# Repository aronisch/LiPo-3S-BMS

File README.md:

# LiPo-3S-BMS
Battery Management System based on bq78350R1 and bq79620 - Designed for 3S LiPo batteries

- Originally created for the [INSA Rennes robot club](https://github.com/clubrobot)
- Schematics and PCB made with Autodesk Eagle
- FETs controlled on the low-side (communication based on ground connection not possible outside the BMS)
- Allow the atmega on the pcb to get the SoC, the voltage, current, remaining time and all the information available from the bq78350R1 (small C++ class using Arduino Wire provided)
- Version 1.1 removes the temperature sensor connector, has a smaller footprint and add a SMB connector for the EV2400 which is the development module necessary to interface the BMS with bqStudio on PC.

## TODO
- Reduce footprint even further
- Change FET control to high-side
- Look for alternatives to the atmega to get battery status (maybe remove it or put the 5V regulator after the protection)
- Use right-angle connectors instead of straight ones
- Better protect SMB port
- Use XT90 Connectors instead of Dean ?

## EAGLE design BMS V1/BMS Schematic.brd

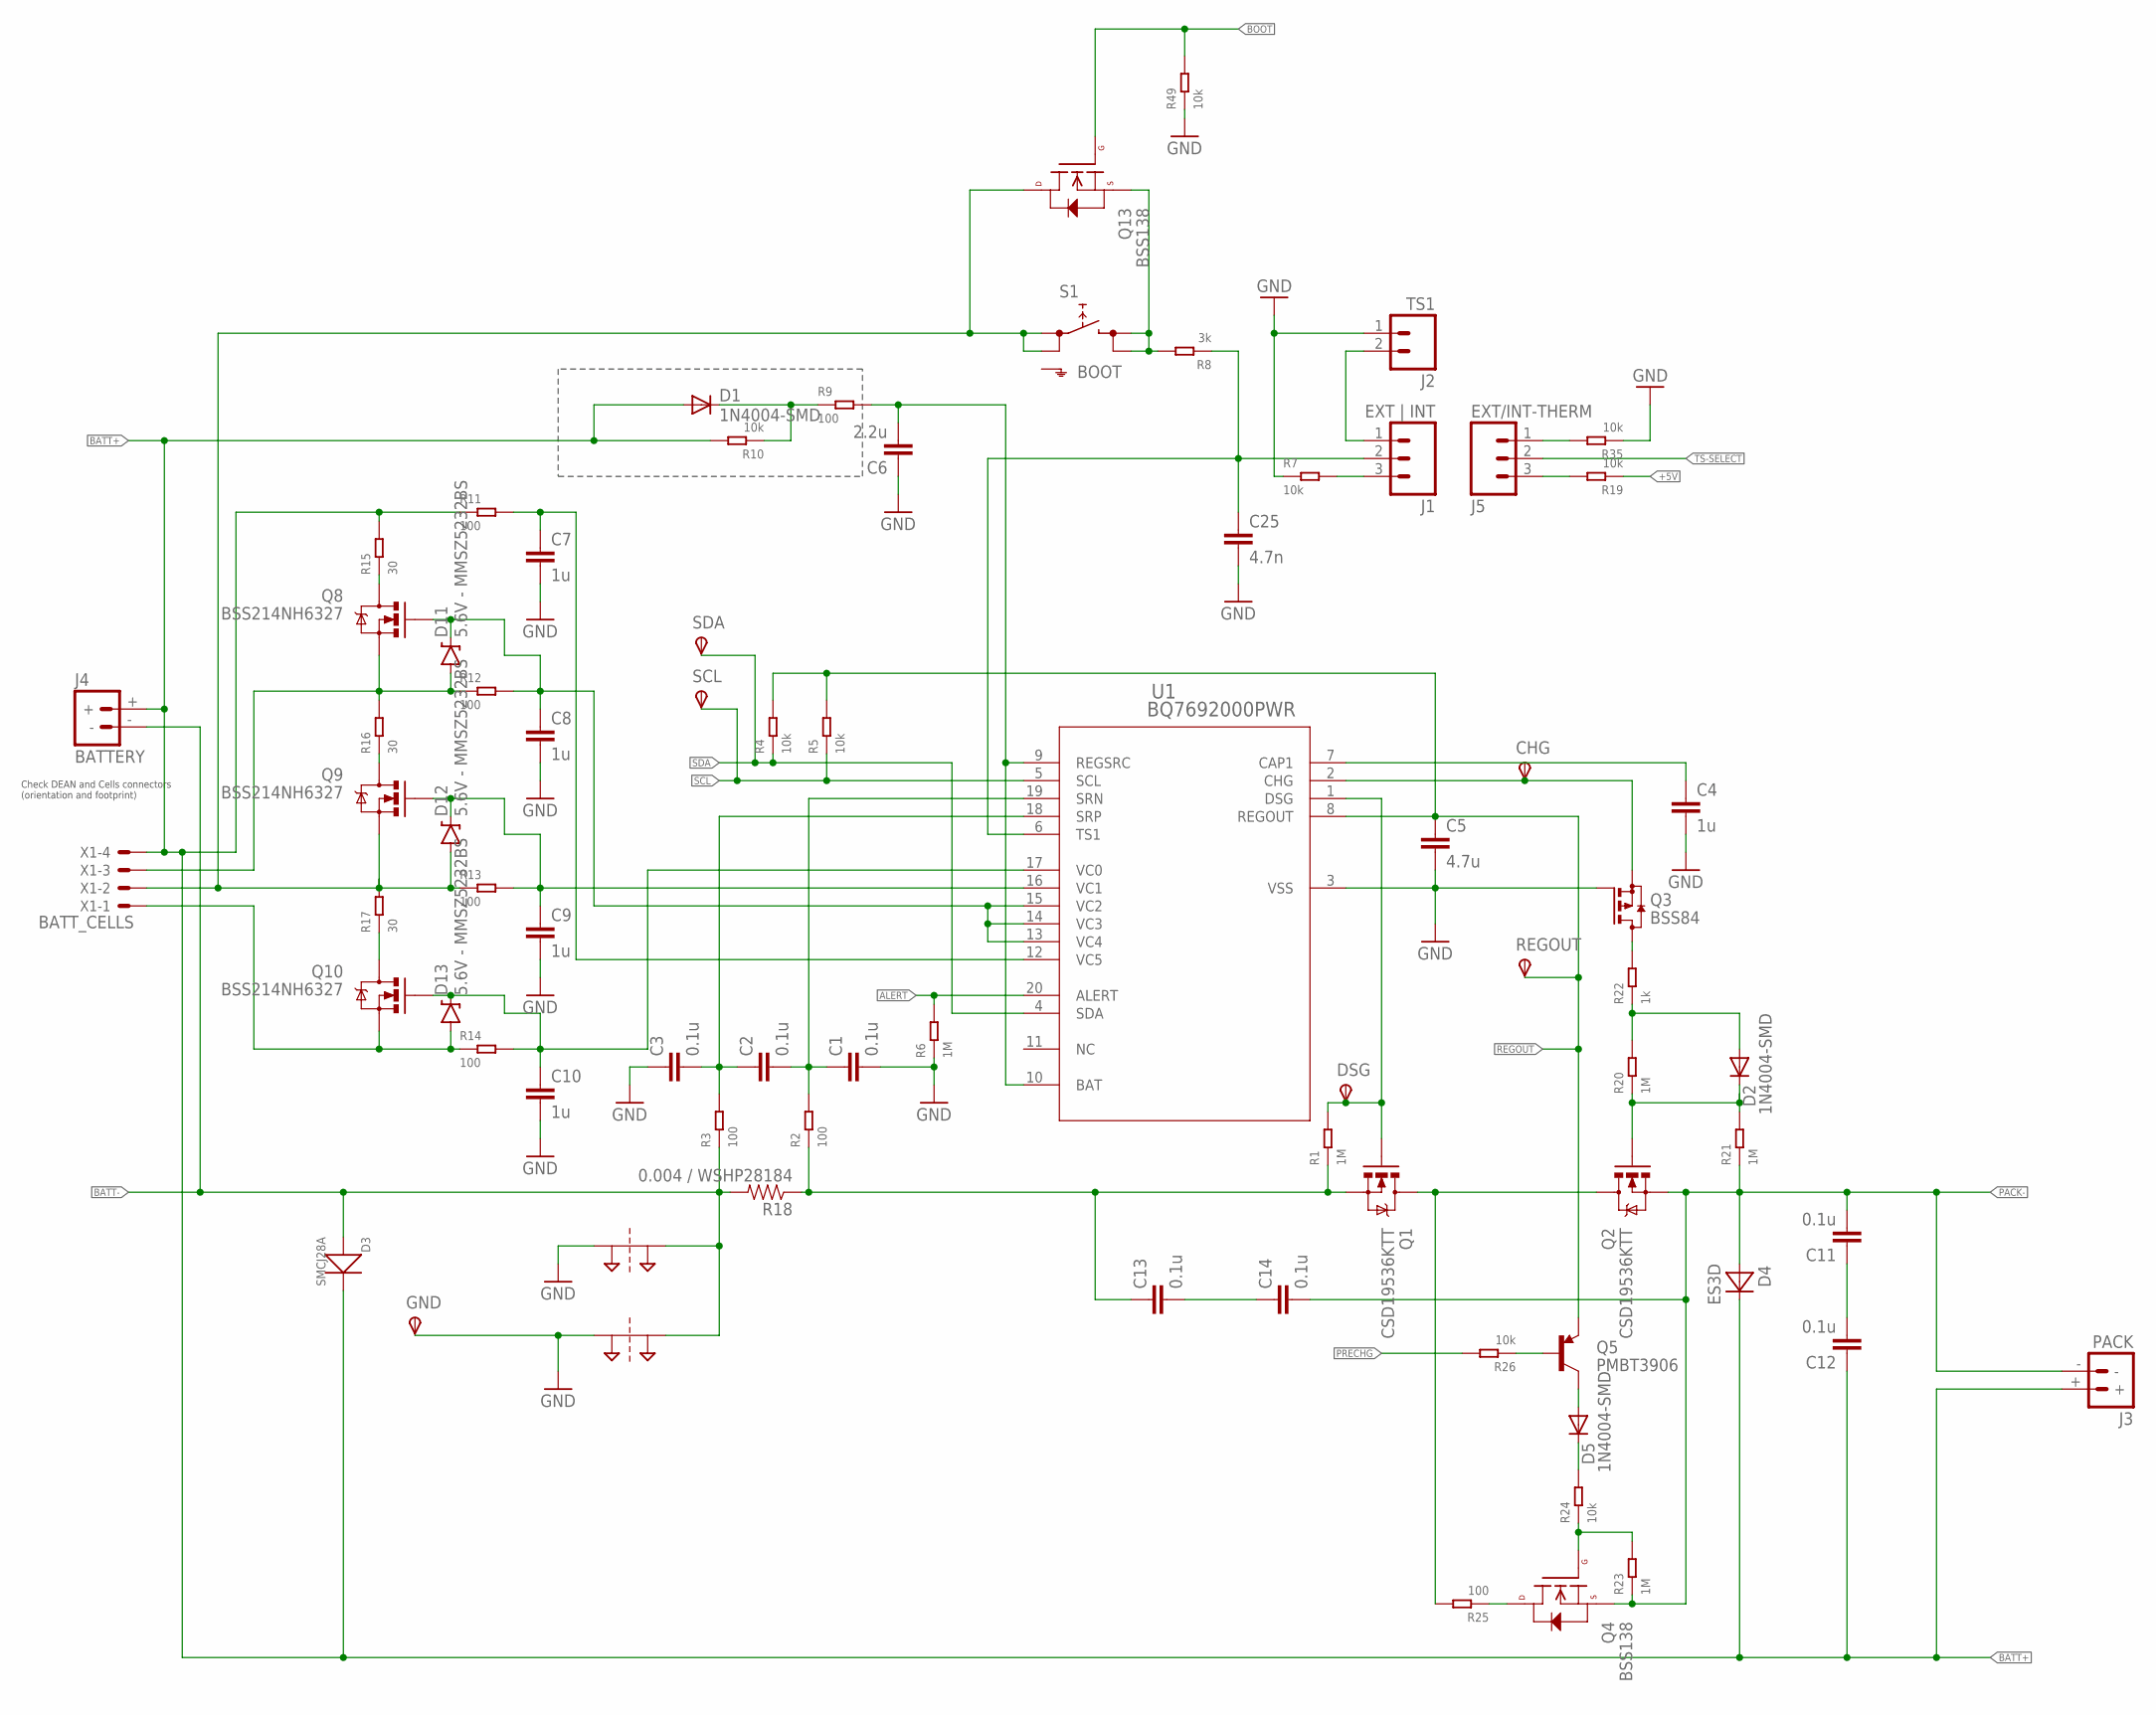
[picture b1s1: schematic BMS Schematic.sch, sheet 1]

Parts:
C1, C2, C3, C11, C12, C13, C14: 0.1u; 0805
C4, C7, C8, C9, C10: 1u; 0805
C5: 4.7u; 0805
C6: 2.2u; C1206
C25: 4.7n; 0805
CHG: TPSB2,54; B2,54
D1, D2, D5: 1N4004-SMD; DO-214
D3: SMCJ28A; DO-214AB
D4: ES3D; SMC
D11, D12, D13: 5.6V - MMSZ5232BS; SOD-323
DSG: TPSB2,54; B2,54
GND: GND; P1-17
J1: EXT | INT; 1X03
J2: TS1; 1X02
J3: PACK; DEANS
J4: BATTERY; DEANS
J5: EXT/INT-THERM; 1X03
PT1, PT2: 2PT_GND_TIE
Q1, Q2: CSD19536KTT; TO-263/D2PAK
Q3: BSS84; SOT23
Q4, Q13: BSS138; SOT23-3
Q5: PMBT3906; SOT23-3
Q8, Q9, Q10: BSS214NH6327; SOT23-3
R1, R6, R20, R21, R23: 1M; R0805
R2, R3, R9, R11, R12, R13, R14: 100; R0805
R4, R5, R7, R10, R19, R24, R26, R35, R49: 10k; R0805
R8: 3k; R0805
R15, R16, R17: 30; R2512
R18: 0.004 / WSHP28184; 2512
R22: 1k; R0805
R25: 100; R2512
REGOUT: TPSB2,54; B2,54
S1: BOOT; SKHMPXE010
SCL: TPSB2,54; B2,54
SDA: TPSB2,54; B2,54
U1: BQ7692000PWR; PW20
X1: BATT_CELLS; 70543-04

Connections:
+5V: R19.1; also elsewhere on the board
ALERT: R6.2, U1.20 (ALERT); also elsewhere on the board
BATT+: C12.1, D1.A, D3.2 (-), D4.C, J3.+, J4.+, R10.2, R11.1, R15.2, X1.4; also elsewhere on the board
BATT-: D3.1 (+), J4.-, PT1.P$2, PT2.P$2, R3.1, R18.2
BOOT: Q13.1 (G), R49.2; also elsewhere on the board
CHG: CHG.TP, Q3.2 (S), U1.2 (CHG)
DSG: DSG.TP, Q1.1 (G), R1.2, U1.1 (DSG)
DSG-CHG: Q1.2 (D), Q2.2 (D), R25.2
GND: C1.2, C3.1, C4.2, C5.2, C6.1, C7.2, C8.2, C9.2, C10.2, C25.2, GND.TP, J2.1, PT1.P$1, PT2.P$1, Q3.1 (G), R6.1, R7.1, R35.1, R49.1, U1.3 (VSS); also elsewhere on the board
unnamed: C2.1, C3.2, R3.2, U1.18 (SRP)
unnamed: C1.1, C2.2, R2.2, U1.19 (SRN)
unnamed: C25.1, J1.2, R8.1, U1.6 (TS1)
unnamed: C6.2, R9.2, U1.9 (REGSRC), U1.10 (BAT)
unnamed: C4.1, U1.7 (CAP1)
unnamed: J1.1, J2.2
unnamed: J1.3, R7.2
unnamed: D1.C, R9.1, R10.1
unnamed: Q13.2 (S), R8.2, S1.3 (2.1), S1.4 (2.2)
unnamed: D13.A, Q10.2 (S), R14.1, X1.1
unnamed: C7.1, R11.2, U1.12 (VC5)
unnamed: Q8.3 (D), R15.1
unnamed: C10.1, D13.C, Q10.1 (G), R14.2, U1.17 (VC0)
unnamed: J5.3, R19.2
unnamed: D11.A, Q8.2 (S), R12.1, R16.2, X1.3
unnamed: Q9.3 (D), R16.1
unnamed: D2.C, Q2.1 (G), R20.1, R21.2
unnamed: C8.1, D11.C, Q8.1 (G), R12.2, U1.13 (VC4), U1.14 (VC3), U1.15 (VC2)
unnamed: Q10.3 (D), R17.1
unnamed: C11.1, C12.2
unnamed: D2.A, R20.2, R22.1
unnamed: D12.A, Q9.2 (S), Q13.3 (D), R13.1, R17.2, S1.1 (1.1), S1.2 (1.2), X1.2
unnamed: Q3.3 (D), R22.2
unnamed: C13.2, C14.1
unnamed: Q4.1 (G), R23.2, R24.1
unnamed: D5.C, R24.2
unnamed: D5.A, Q5.3 (C)
unnamed: Q5.1 (B), R26.1
unnamed: Q4.3 (D), R25.1
unnamed: J5.1, R35.2
unnamed: C9.1, D12.C, Q9.1 (G), R13.2, U1.16 (VC1)
PACK-: C11.2, C14.2, D4.A, J3.-, Q2.3 (S), Q4.2 (S), R21.1, R23.1
PRECHG: R26.2; also elsewhere on the board
REGOUT: C5.1, Q5.2 (E), R4.2, R5.2, REGOUT.TP, U1.8 (REGOUT); also elsewhere on the board
RSNS-DSG: C13.1, Q1.3 (S), R1.1, R2.1, R18.1
SCL: R5.1, SCL.TP, U1.5 (SCL); also elsewhere on the board
SDA: R4.1, SDA.TP, U1.4 (SDA); also elsewhere on the board
TS-SELECT: J5.2; also elsewhere on the board

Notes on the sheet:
Check DEAN and Cells connectors (orientation and footprint)

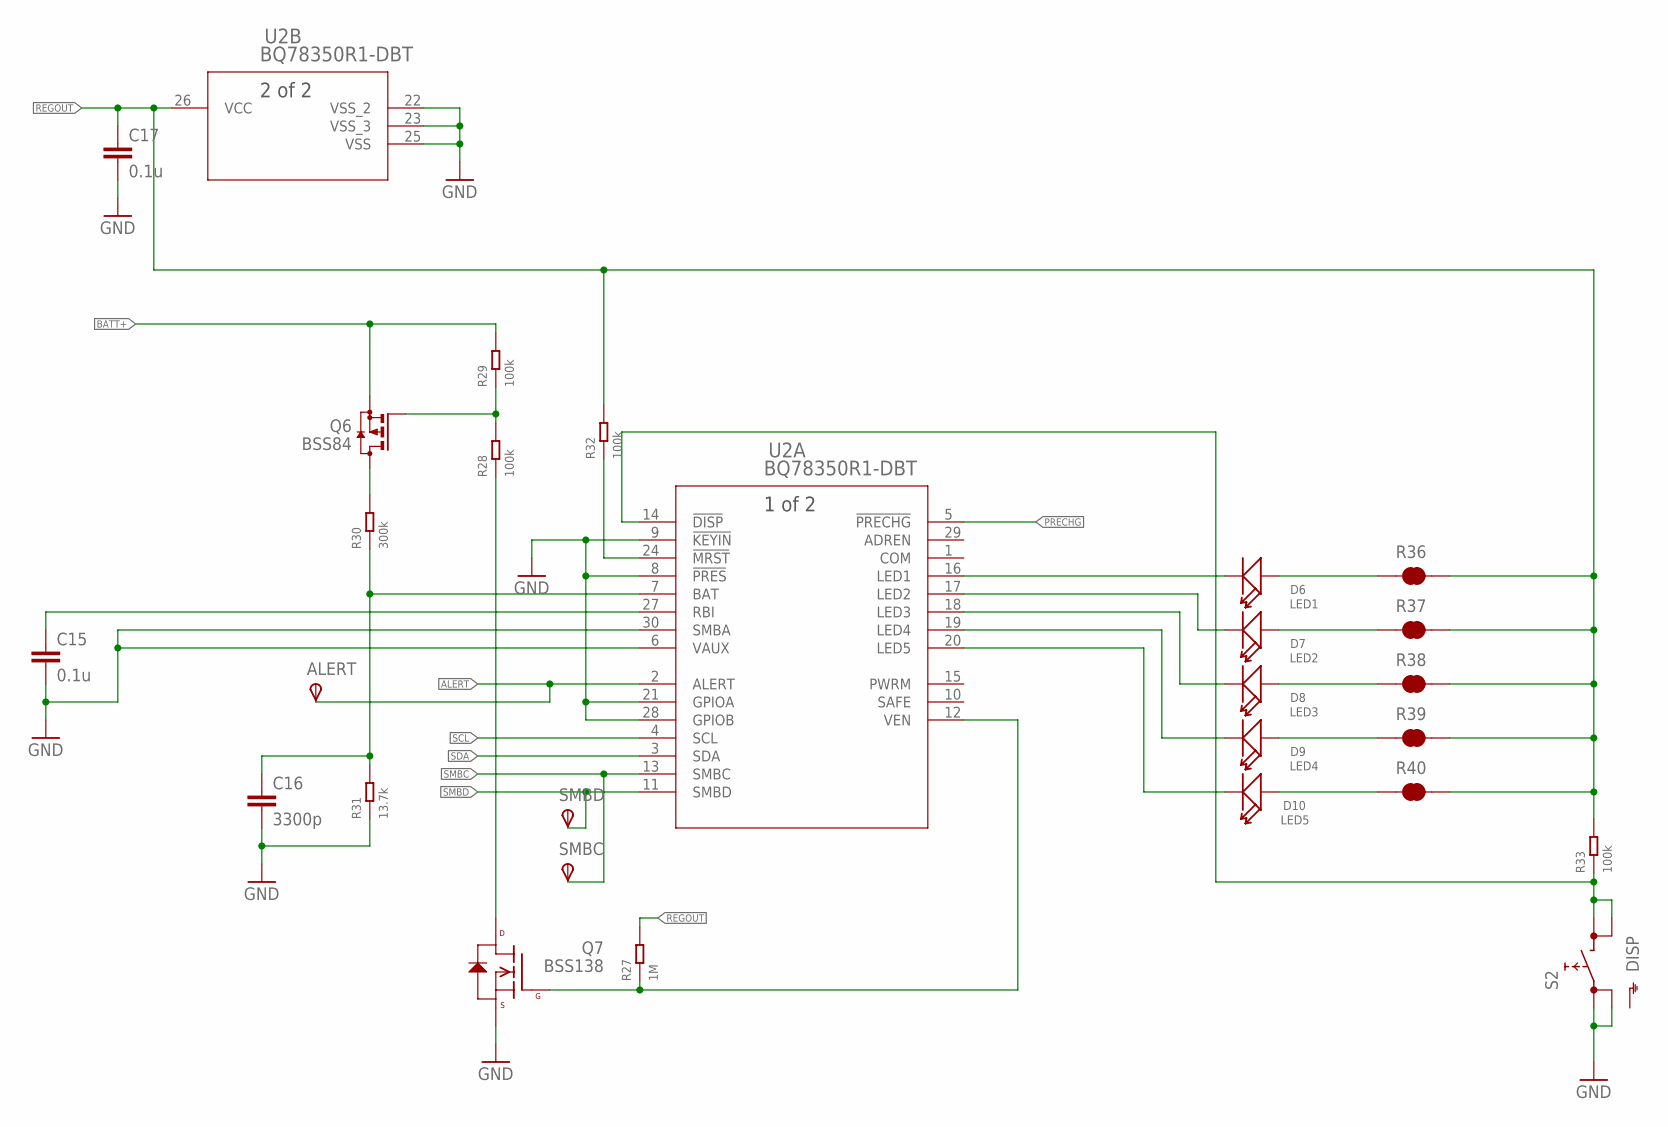
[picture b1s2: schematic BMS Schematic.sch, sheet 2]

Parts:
ALERT: TPSB2,54; B2,54
C15, C17: 0.1u; 0805
C16: 3300p; 0805
D6: LED1; LED-0805
D7: LED2; LED-0805
D8: LED3; LED-0805
D9: LED4; LED-0805
D10: LED5; LED-0805
Q6: BSS84; SOT23
Q7: BSS138; SOT23-3
R27: 1M; R0805
R28, R29, R32, R33: 100k; R0805
R30: 300k; R0805
R31: 13.7k; R0805
R36, R37, R38, R39, R40: JUMPER-NC-0805; R0805
S2: DISP; SKHMPXE010
SMBC: TPSB2,54; B2,54
SMBD: TPSB2,54; B2,54
U2: BQ78350R1-DBT; DBT30

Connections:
ALERT: ALERT.TP, U2.2 (ALERT); also elsewhere on the board
BATT+: Q6.2 (S), R29.2; also elsewhere on the board
GND: C15.2, C16.2, C17.2, Q7.2 (S), R31.1, S2.1 (1.1), S2.2 (1.2), U2.6 (VAUX), U2.8 (!PRES), U2.9 (!KEYIN), U2.21 (GPIOA), U2.22 (VSS_2), U2.23 (VSS_3), U2.25 (VSS), U2.28 (GPIOB), U2.30 (SMBA); also elsewhere on the board
unnamed: C15.1, U2.27 (RBI)
unnamed: Q7.1 (G), R27.1, U2.12 (VEN)
unnamed: Q7.3 (D), R28.1
unnamed: Q6.1 (G), R28.2, R29.1
unnamed: Q6.3 (D), R30.2
unnamed: C16.1, R30.1, R31.2, U2.7 (BAT)
unnamed: R32.1, U2.24 (!MRST)
unnamed: D6.-, U2.16 (LED1)
unnamed: D7.-, U2.17 (LED2)
unnamed: D8.-, U2.18 (LED3)
unnamed: D9.-, U2.19 (LED4)
unnamed: D10.-, U2.20 (LED5)
unnamed: D6.+, R36.1
unnamed: D7.+, R37.1
unnamed: R33.1, S2.3 (2.1), S2.4 (2.2), U2.14 (!DISP)
unnamed: D8.+, R38.1
unnamed: D9.+, R39.1
unnamed: D10.+, R40.1
PRECHG: U2.5 (!PRECHG); also elsewhere on the board
REGOUT: C17.1, R27.2, R32.2, R33.2, R36.2, R37.2, R38.2, R39.2, R40.2, U2.26 (VCC); also elsewhere on the board
SCL: U2.4 (SCL); also elsewhere on the board
SDA: U2.3 (SDA); also elsewhere on the board
SMBC: SMBC.TP, U2.13 (SMBC); also elsewhere on the board
SMBD: SMBD.TP, U2.11 (SMBD); also elsewhere on the board

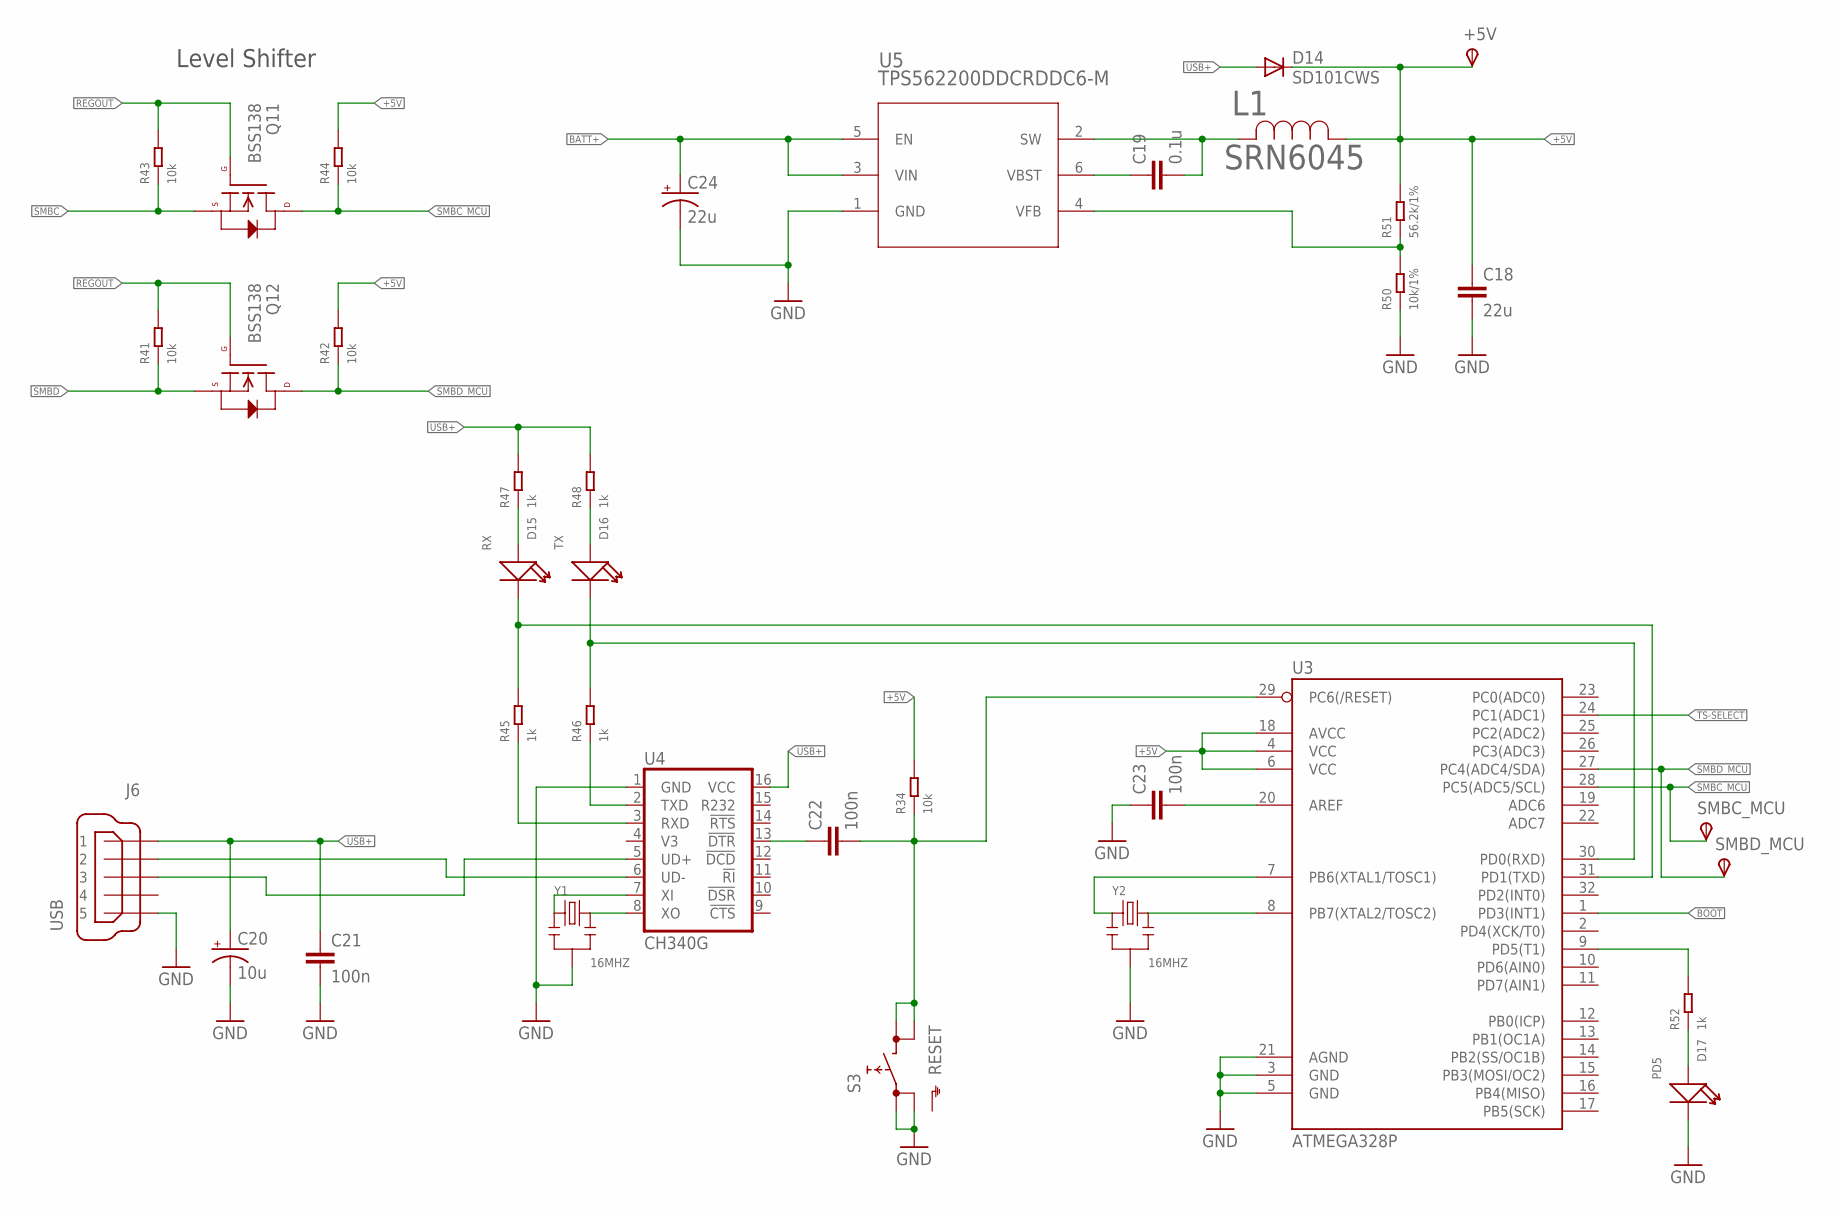
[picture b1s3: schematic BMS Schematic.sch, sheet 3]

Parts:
+5V: TPSB2,54; B2,54
C18: 22u; 0805
C19: 0.1u; 0805
C20: 10u; EIA3216-KIT
C21, C22, C23: 100n; 0603-CAP
C24: 22u; PANASONIC_C
D14: SD101CWS; SOD323-W
D15: RX; LED-0805
D16: TX; LED-0805
D17: PD5; LED-0805
J6: USB; USB-MINI-B_2
L1: SRN6045; IND_BOURNS_SRN6045
Q11, Q12: BSS138; SOT23-3
R34, R41, R42, R43, R44: 10k; R0805
R45, R46, R47, R48, R52: 1k; R0805
R50: 10k/1%; R0805
R51: 56.2k/1%; R0805
S3: RESET; SKHMPXE010
SMBC_MCU: TPSB2,54; B2,54
SMBD_MCU: TPSB2,54; B2,54
U3: ATMEGA328P; TQFP32-08
U4: CH340G; SO016
U5: TPS562200DDCRDDC6-M; DDC6-M
Y1, Y2: 16MHZ; X3-SMD-3.6X1.3X0.8MM

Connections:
+5V: +5V.TP, C18.1, D14.C, L1.1, R34.2, R42.2, R44.2, R51.2, U3.4 (VCC), U3.6 (VCC), U3.18 (AVCC); also elsewhere on the board
BATT+: C24.+, U5.3 (VIN), U5.5 (EN); also elsewhere on the board
BOOT: U3.1 (PD3(INT1)); also elsewhere on the board
GND: C18.2, C20.C (-), C21.2, C23.1, C24.-, D17.-, J6.1 (5), R50.1, S3.1 (1.1), S3.2 (1.2), U3.3 (GND), U3.5 (GND), U3.21 (AGND), U4.1 (GND), U5.1 (GND), Y1.2, Y2.2; also elsewhere on the board
unnamed: J6.4 (2), U4.6 (UD-)
unnamed: J6.3, U4.5 (UD+)
unnamed: D15.+, R47.1
unnamed: D16.+, R48.1
unnamed: C22.1, U4.13 (!DTR)
unnamed: C22.2, R34.1, S3.3 (2.1), S3.4 (2.2), U3.29 (PC6(/RESET))
unnamed: U4.7 (XI), Y1.1
unnamed: U4.8 (XO), Y1.3
unnamed: R45.1, U4.3 (RXD)
unnamed: U3.8 (PB7(XTAL2/TOSC2)), Y2.3
unnamed: U3.7 (PB6(XTAL1/TOSC1)), Y2.1
unnamed: R46.1, U4.2 (TXD)
unnamed: D15.-, R45.2, U3.31 (PD1(TXD))
unnamed: D16.-, R46.2, U3.30 (PD0(RXD))
unnamed: C23.2, U3.20 (AREF)
unnamed: R50.2, R51.1, U5.4 (VFB)
unnamed: C19.1, U5.6 (VBST)
unnamed: R52.2, U3.9 (PD5(T1))
unnamed: D17.+, R52.1
REGOUT: Q11.1 (G), Q12.1 (G), R41.2, R43.2; also elsewhere on the board
SMBC: Q11.2 (S), R43.1; also elsewhere on the board
SMBC_MCU: Q11.3 (D), R44.1, SMBC_MCU.TP, U3.28 (PC5(ADC5/SCL))
SMBD: Q12.2 (S), R41.1; also elsewhere on the board
SMBD_MCU: Q12.3 (D), R42.1, SMBD_MCU.TP, U3.27 (PC4(ADC4/SDA))
SW: C19.2, L1.2, U5.2 (SW)
TS-SELECT: U3.24 (PC1(ADC1)); also elsewhere on the board
USB+: C20.A (+), C21.1, D14.A, J6.5 (1), R47.2, R48.2, U4.16 (VCC)

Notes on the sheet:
Level Shifter

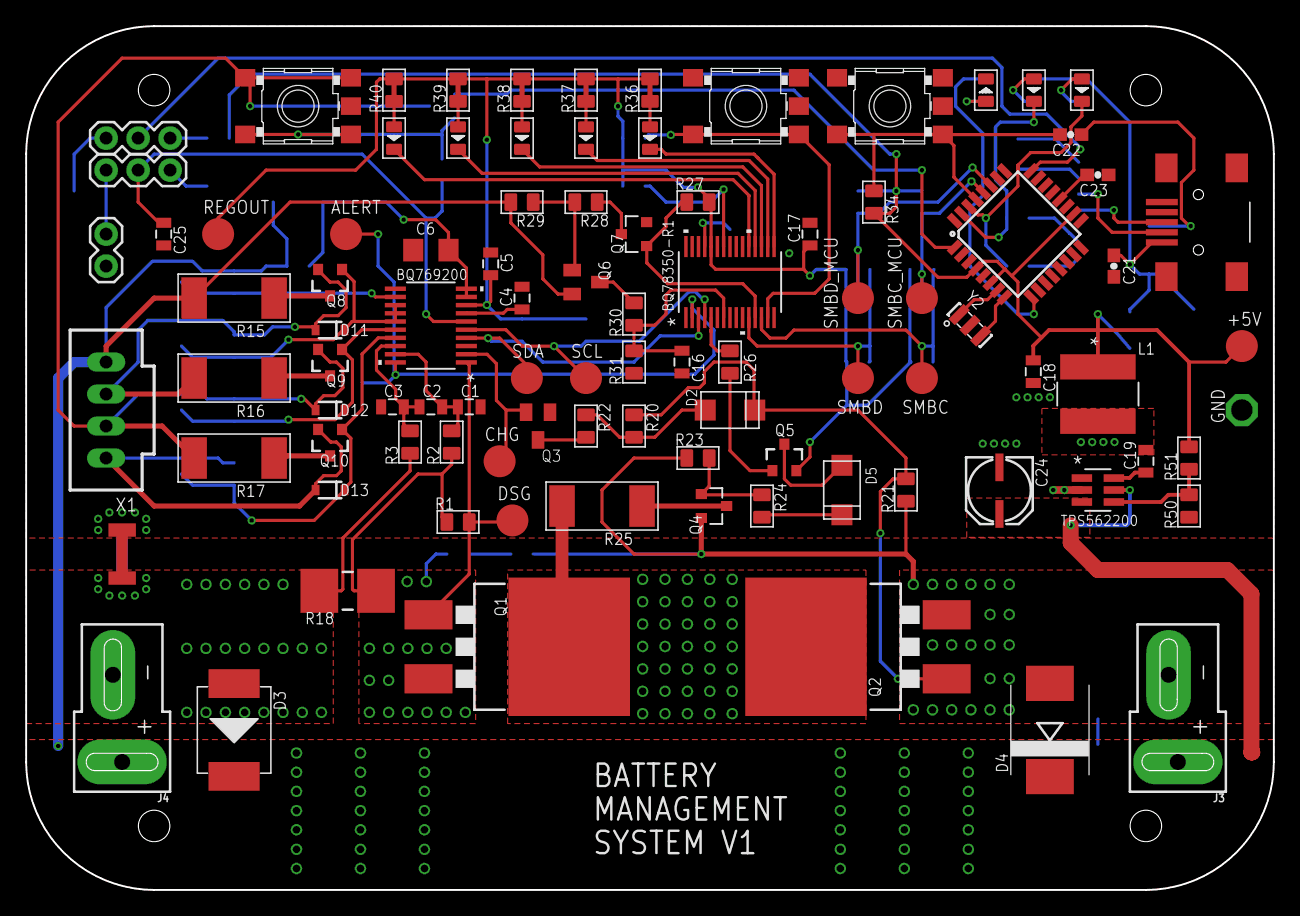
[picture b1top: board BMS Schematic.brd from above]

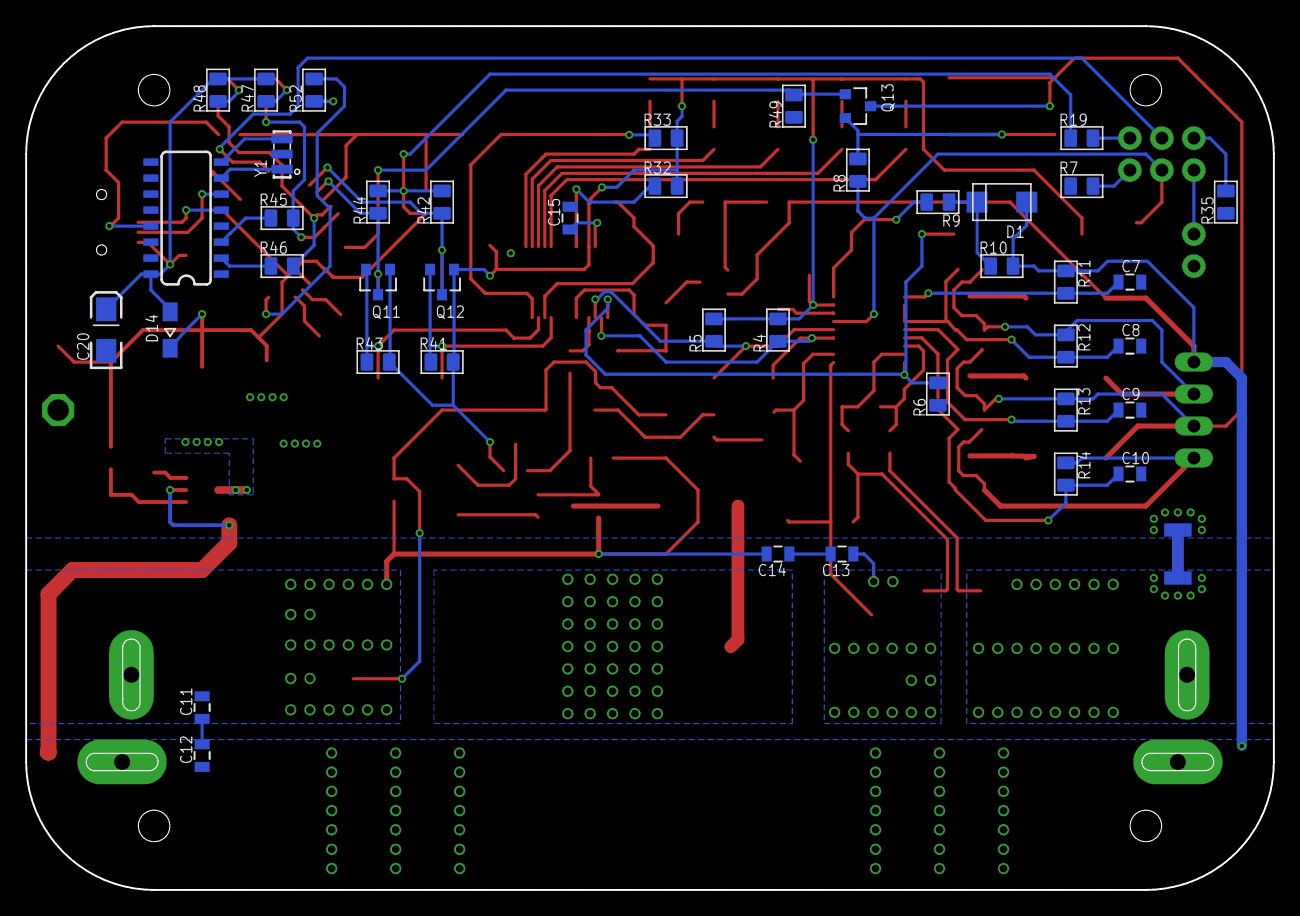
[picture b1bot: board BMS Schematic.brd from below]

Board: 2 copper layers, 99.1 x 68.6 mm, 139 parts (43 on the bottom side), 90 nets.

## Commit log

2018-11-19 Initial README.md
2018-11-19 Add V1 and V1.1 eagle files with first bms lib
2018-11-19 Rename BMS Schematic.html to BMS BOM.html
2019-02-28 Update TODO List

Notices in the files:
parts and their libraries:
SparkFun-Passives: Licensing: Creative Commons ShareAlike 4.0 International - https://creativecommons.org/licenses/by-sa/4.0
